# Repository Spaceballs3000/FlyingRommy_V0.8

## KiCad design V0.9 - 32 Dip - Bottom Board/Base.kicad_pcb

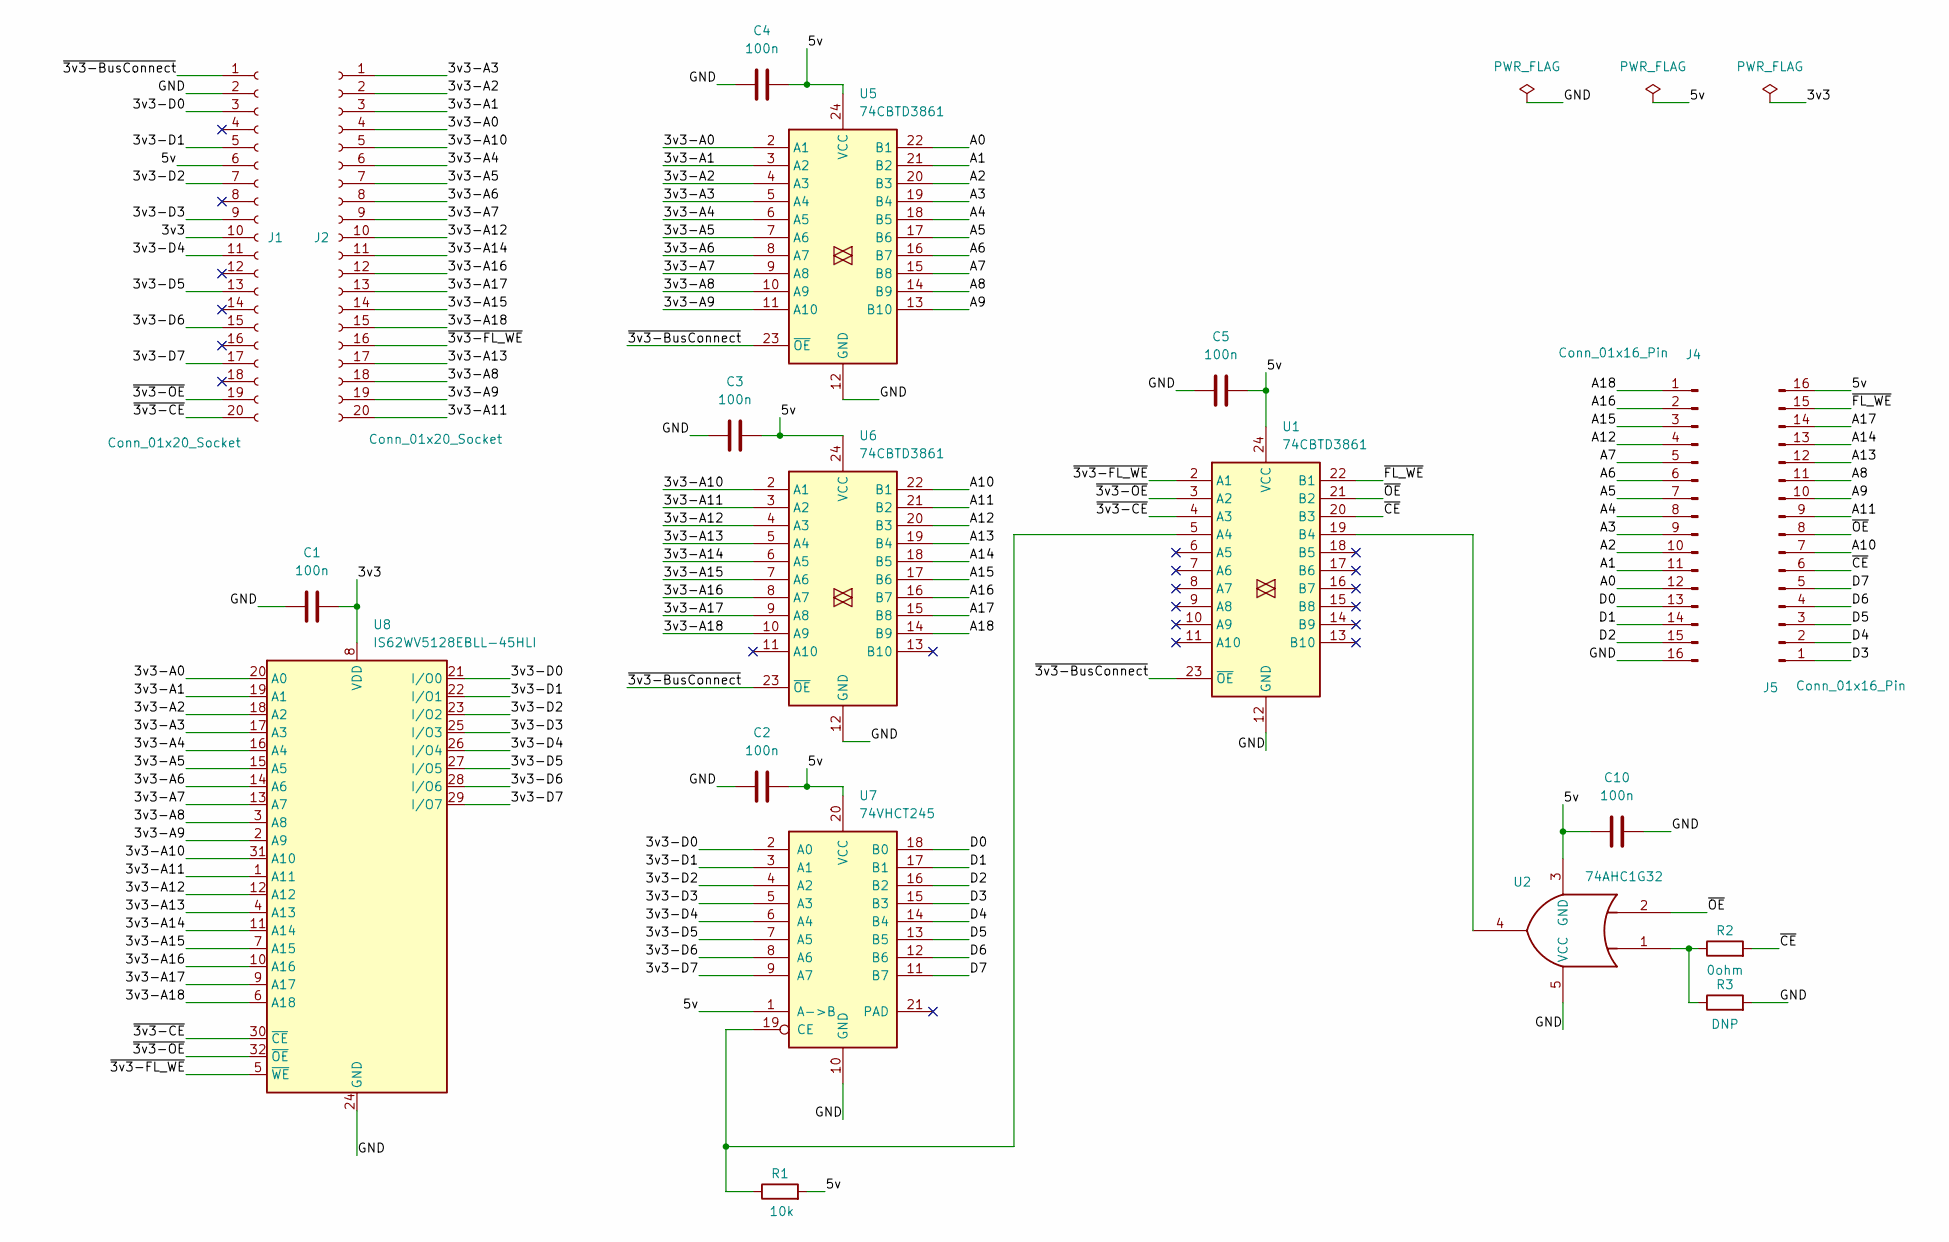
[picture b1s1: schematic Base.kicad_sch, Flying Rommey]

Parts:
C1, C2, C3, C4, C5, C10: 100n; C_0603_1608Metric
J1, J2: Conn_01x20_Socket; PinSocket_2x10_P1.00mm_Vertical_SMD
J4, J5: Conn_01x16_Pin; PinHeader_1x16_P2.54mm_Vertical
R1: 10k; R_0402_1005Metric
R2: 0ohm; R_0402_1005Metric
R3: DNP; R_0402_1005Metric
U1, U5, U6: 74CBTD3861; SSOP-24_3.9x8.7mm_P0.635mm
U2: 74AHC1G32; SOT-353_SC-70-5
U7: 74VHCT245; DHVQFN-20-1EP_2.5x4.5mm_P0.5mm_EP1x3mm
U8: IS62WV5128EBLL-45HLI; TSOP-I-32_11.8x8mm_P0.5mm

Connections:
/3v3: C1.1, J1.10, U8.8 (VDD)
/3v3-A0: J2.4, U5.2 (A1), U8.20 (A0)
/3v3-A1: J2.3, U5.3 (A2), U8.19 (A1)
/3v3-A2: J2.2, U5.4 (A3), U8.18 (A2)
/3v3-A3: J2.1, U5.5 (A4), U8.17 (A3)
/3v3-A4: J2.6, U5.6 (A5), U8.16 (A4)
/3v3-A5: J2.7, U5.7 (A6), U8.15 (A5)
/3v3-A6: J2.8, U5.8 (A7), U8.14 (A6)
/3v3-A7: J2.9, U5.9 (A8), U8.13 (A7)
/3v3-A8: J2.18, U5.10 (A9), U8.3 (A8)
/3v3-A9: J2.19, U5.11 (A10), U8.2 (A9)
/3v3-A10: J2.5, U6.2 (A1), U8.31 (A10)
/3v3-A11: J2.20, U6.3 (A2), U8.1 (A11)
/3v3-A12: J2.10, U6.4 (A3), U8.12 (A12)
/3v3-A13: J2.17, U6.5 (A4), U8.4 (A13)
/3v3-A14: J2.11, U6.6 (A5), U8.11 (A14)
/3v3-A15: J2.14, U6.7 (A6), U8.7 (A15)
/3v3-A16: J2.12, U6.8 (A7), U8.10 (A16)
/3v3-A17: J2.13, U6.9 (A8), U8.9 (A17)
/3v3-A18: J2.15, U6.10 (A9), U8.6 (A18)
/3v3-D0: J1.3, U7.2 (A0), U8.21 (I/O0)
/3v3-D1: J1.5, U7.3 (A1), U8.22 (I/O1)
/3v3-D2: J1.7, U7.4 (A2), U8.23 (I/O2)
/3v3-D3: J1.9, U7.5 (A3), U8.25 (I/O3)
/3v3-D4: J1.11, U7.6 (A4), U8.26 (I/O4)
/3v3-D5: J1.13, U7.7 (A5), U8.27 (I/O5)
/3v3-D6: J1.15, U7.8 (A6), U8.28 (I/O6)
/3v3-D7: J1.17, U7.9 (A7), U8.29 (I/O7)
/5v: C2.1, C3.1, C4.1, C5.1, C10.2, J1.6, J5.16, R1.2, U1.24 (VCC), U2.3 (GND), U5.24 (VCC), U6.24 (VCC), U7.1 (A->B), U7.20 (VCC)
/A0: J4.12, U5.22 (B1)
/A1: J4.11, U5.21 (B2)
/A2: J4.10, U5.20 (B3)
/A3: J4.9, U5.19 (B4)
/A4: J4.8, U5.18 (B5)
/A5: J4.7, U5.17 (B6)
/A6: J4.6, U5.16 (B7)
/A7: J4.5, U5.15 (B8)
/A8: J5.11, U5.14 (B9)
/A9: J5.10, U5.13 (B10)
/A10: J5.7, U6.22 (B1)
/A11: J5.9, U6.21 (B2)
/A12: J4.4, U6.20 (B3)
/A13: J5.12, U6.19 (B4)
/A14: J5.13, U6.18 (B5)
/A15: J4.3, U6.17 (B6)
/A16: J4.2, U6.16 (B7)
/A17: J5.14, U6.15 (B8)
/A18: J4.1, U6.14 (B9)
/D0: J4.13, U7.18 (B0)
/D1: J4.14, U7.17 (B1)
/D2: J4.15, U7.16 (B2)
/D3: J5.1, U7.15 (B3)
/D4: J5.2, U7.14 (B4)
/D5: J5.3, U7.13 (B5)
/D6: J5.4, U7.12 (B6)
/D7: J5.5, U7.11 (B7)
/GND: C1.2, C2.2, C3.2, C4.2, C5.2, C10.1, J1.2, J4.16, R3.2, U1.12 (GND), U2.5 (VCC), U5.12 (GND), U6.12 (GND), U7.10 (GND), U8.24 (GND)
/~3v3-BusConnect: J1.1, U1.23 (~OE), U5.23 (~OE), U6.23 (~OE)
/~3v3-CE: J1.20, U1.4 (A3), U8.30 (~CE)
/~3v3-FL_WE: J2.16, U1.2 (A1), U8.5 (~WE)
/~3v3-OE: J1.19, U1.3 (A2), U8.32 (~OE)
/~CE: J5.6, R2.2, U1.20 (B3)
/~FL_WE: J5.15, U1.22 (B1)
/~OE: J5.8, U1.21 (B2), U2.2
unnamed: R2.1, R3.1, U2.1
unnamed: R1.1, U1.5 (A4), U7.19 (CE)
unnamed: U1.19 (B4), U2.4

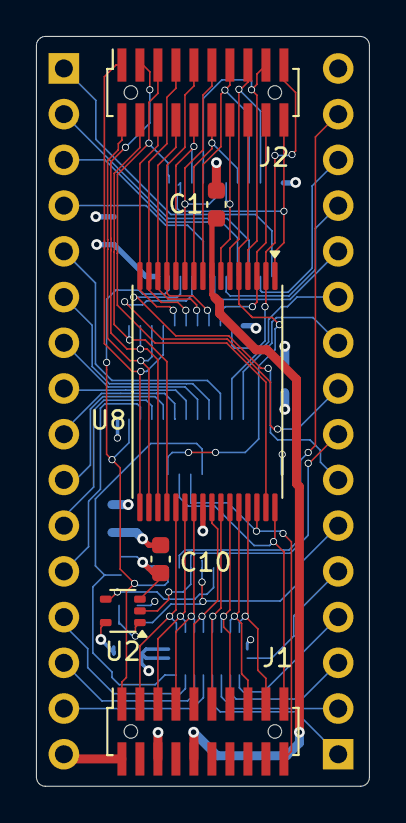
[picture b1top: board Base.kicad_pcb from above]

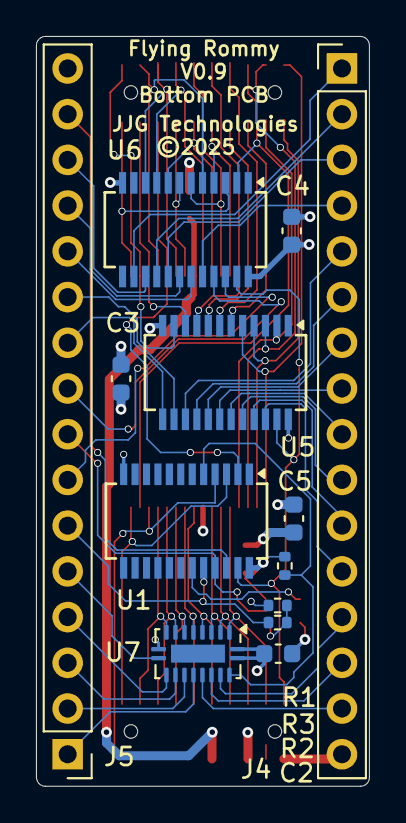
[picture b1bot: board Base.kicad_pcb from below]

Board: 4 copper layers, 18.5 x 41.7 mm, 19 parts (13 on the bottom side), 67 nets.

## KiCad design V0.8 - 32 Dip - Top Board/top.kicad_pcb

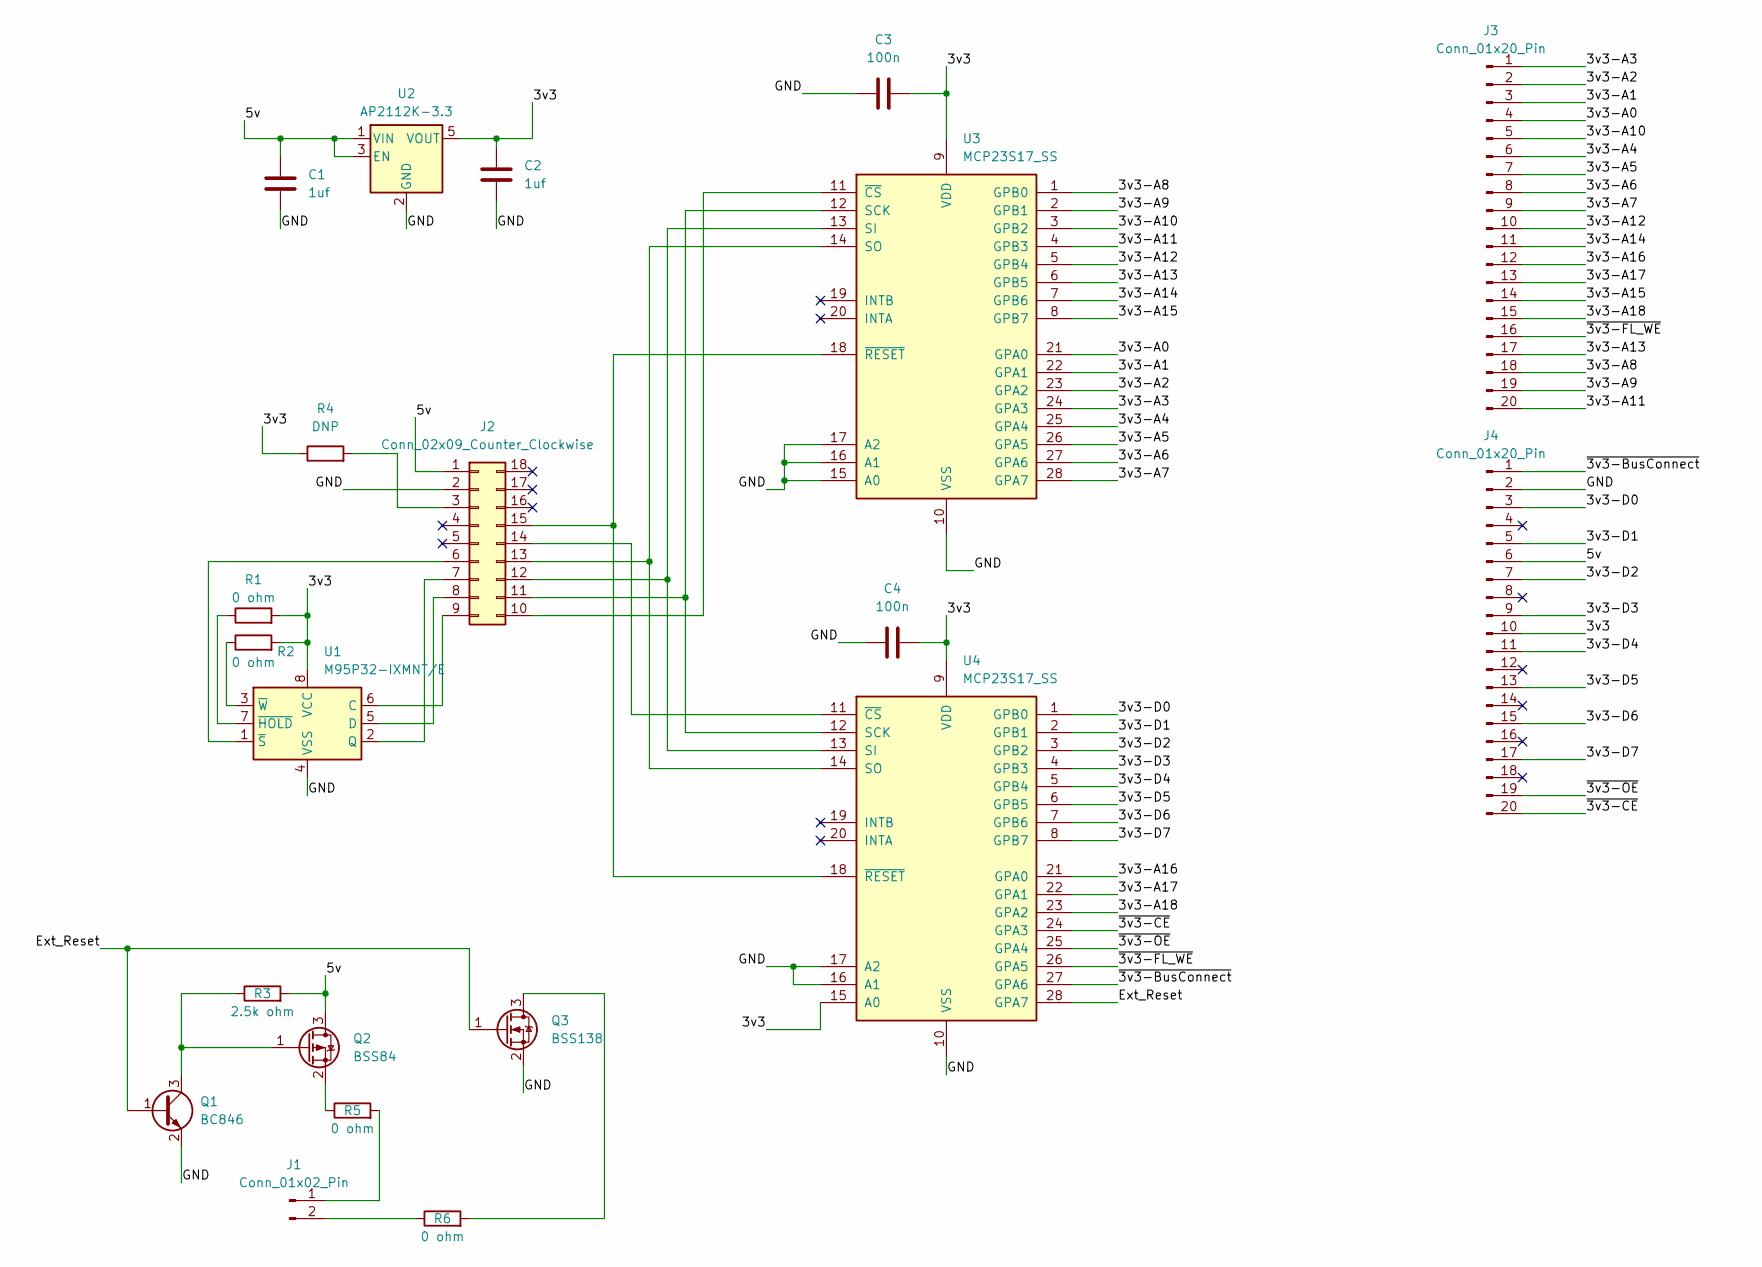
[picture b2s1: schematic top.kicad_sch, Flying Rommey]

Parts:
C1, C2: 1uf; C_0402_1005Metric
C3, C4: 100n; C_0603_1608Metric
J1: Conn_01x02_Pin; PinHeader_1x02_P2.54mm_Horizontal
J2: Conn_02x09_Counter_Clockwise; ESP32
J3, J4: Conn_01x20_Pin; PinHeader_2x10_P1.00mm_Vertical_SMD
Q1: BC846; SOT-23
Q2: BSS84; SOT-23
Q3: BSS138; SOT-23
R1, R2, R5, R6: 0 ohm; R_0402_1005Metric
R3: 2.5k ohm; R_0402_1005Metric
R4: DNP; R_0402_1005Metric
U1: M95P32-IXMNT/E; SOIC-8_3.9x4.9mm_P1.27mm
U2: AP2112K-3.3; SOT-23-5
U3, U4: MCP23S17_SS; SSOP-28_5.3x10.2mm_P0.65mm

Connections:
/3v3: C2.1, C3.1, C4.1, J4.10, R1.2, R2.2, R4.1, U1.8 (VCC), U2.5 (VOUT), U3.9 (VDD), U4.9 (VDD), U4.15 (A0)
/3v3-A0: J3.4, U3.21 (GPA0)
/3v3-A1: J3.3, U3.22 (GPA1)
/3v3-A2: J3.2, U3.23 (GPA2)
/3v3-A3: J3.1, U3.24 (GPA3)
/3v3-A4: J3.6, U3.25 (GPA4)
/3v3-A5: J3.7, U3.26 (GPA5)
/3v3-A6: J3.8, U3.27 (GPA6)
/3v3-A7: J3.9, U3.28 (GPA7)
/3v3-A8: J3.18, U3.1 (GPB0)
/3v3-A9: J3.19, U3.2 (GPB1)
/3v3-A10: J3.5, U3.3 (GPB2)
/3v3-A11: J3.20, U3.4 (GPB3)
/3v3-A12: J3.10, U3.5 (GPB4)
/3v3-A13: J3.17, U3.6 (GPB5)
/3v3-A14: J3.11, U3.7 (GPB6)
/3v3-A15: J3.14, U3.8 (GPB7)
/3v3-A16: J3.12, U4.21 (GPA0)
/3v3-A17: J3.13, U4.22 (GPA1)
/3v3-A18: J3.15, U4.23 (GPA2)
/3v3-D0: J4.3, U4.1 (GPB0)
/3v3-D1: J4.5, U4.2 (GPB1)
/3v3-D2: J4.7, U4.3 (GPB2)
/3v3-D3: J4.9, U4.4 (GPB3)
/3v3-D4: J4.11, U4.5 (GPB4)
/3v3-D5: J4.13, U4.6 (GPB5)
/3v3-D6: J4.15, U4.7 (GPB6)
/3v3-D7: J4.17, U4.8 (GPB7)
/5v: C1.1, J2.1, J4.6, Q2.3 (D), R3.2, U2.1 (VIN), U2.3 (EN)
/Ext_Reset: Q1.1 (B), Q3.1 (G), U4.28 (GPA7)
/GND: C1.2, C2.2, C3.2, C4.2, J2.2, J4.2, Q1.2 (E), Q3.2 (S), U1.4 (VSS), U2.2 (GND), U3.10 (VSS), U3.15 (A0), U3.16 (A1), U3.17 (A2), U4.10 (VSS), U4.16 (A1), U4.17 (A2)
/~3v3-BusConnect: J4.1, U4.27 (GPA6)
/~3v3-CE: J4.20, U4.24 (GPA3)
/~3v3-FL_WE: J3.16, U4.26 (GPA5)
/~3v3-OE: J4.19, U4.25 (GPA4)
unnamed: J1.1, R5.2
unnamed: J1.2, R6.1
unnamed: J2.3, R4.2
unnamed: J2.6, U1.1 (~S)
unnamed: J2.7, U1.2 (Q)
unnamed: J2.8, U1.5 (D)
unnamed: J2.9, U1.6 (C)
unnamed: J2.10, U3.11 (~CS)
unnamed: J2.11, U3.12 (SCK), U4.12 (SCK)
unnamed: J2.12, U3.13 (SI), U4.13 (SI)
unnamed: J2.13, U3.14 (SO), U4.14 (SO)
unnamed: J2.14, U4.11 (~CS)
unnamed: J2.15, U3.18 (~RESET), U4.18 (~RESET)
unnamed: Q1.3 (C), Q2.1 (G), R3.1
unnamed: Q2.2 (S), R5.1
unnamed: Q3.3 (D), R6.2
unnamed: R1.1, U1.7 (~HOLD)
unnamed: R2.1, U1.3 (~W)

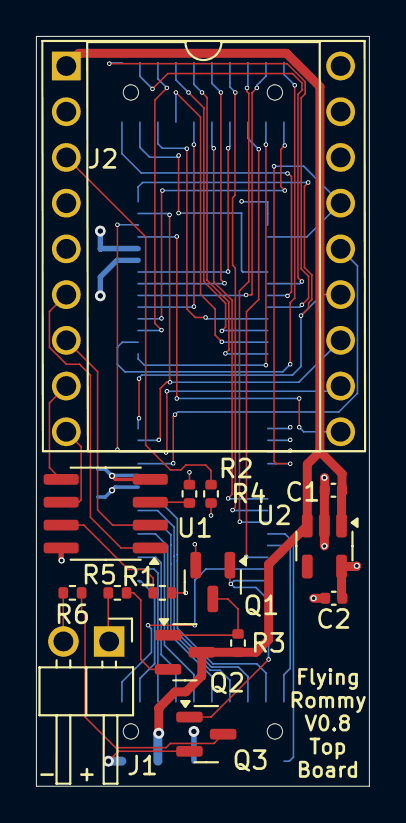
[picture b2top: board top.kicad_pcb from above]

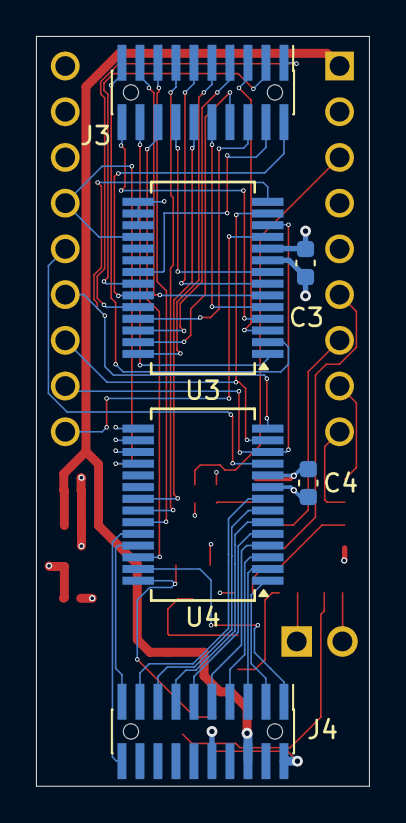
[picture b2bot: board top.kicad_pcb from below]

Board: 4 copper layers, 18.5 x 41.7 mm, 21 parts (6 on the bottom side), 53 nets.

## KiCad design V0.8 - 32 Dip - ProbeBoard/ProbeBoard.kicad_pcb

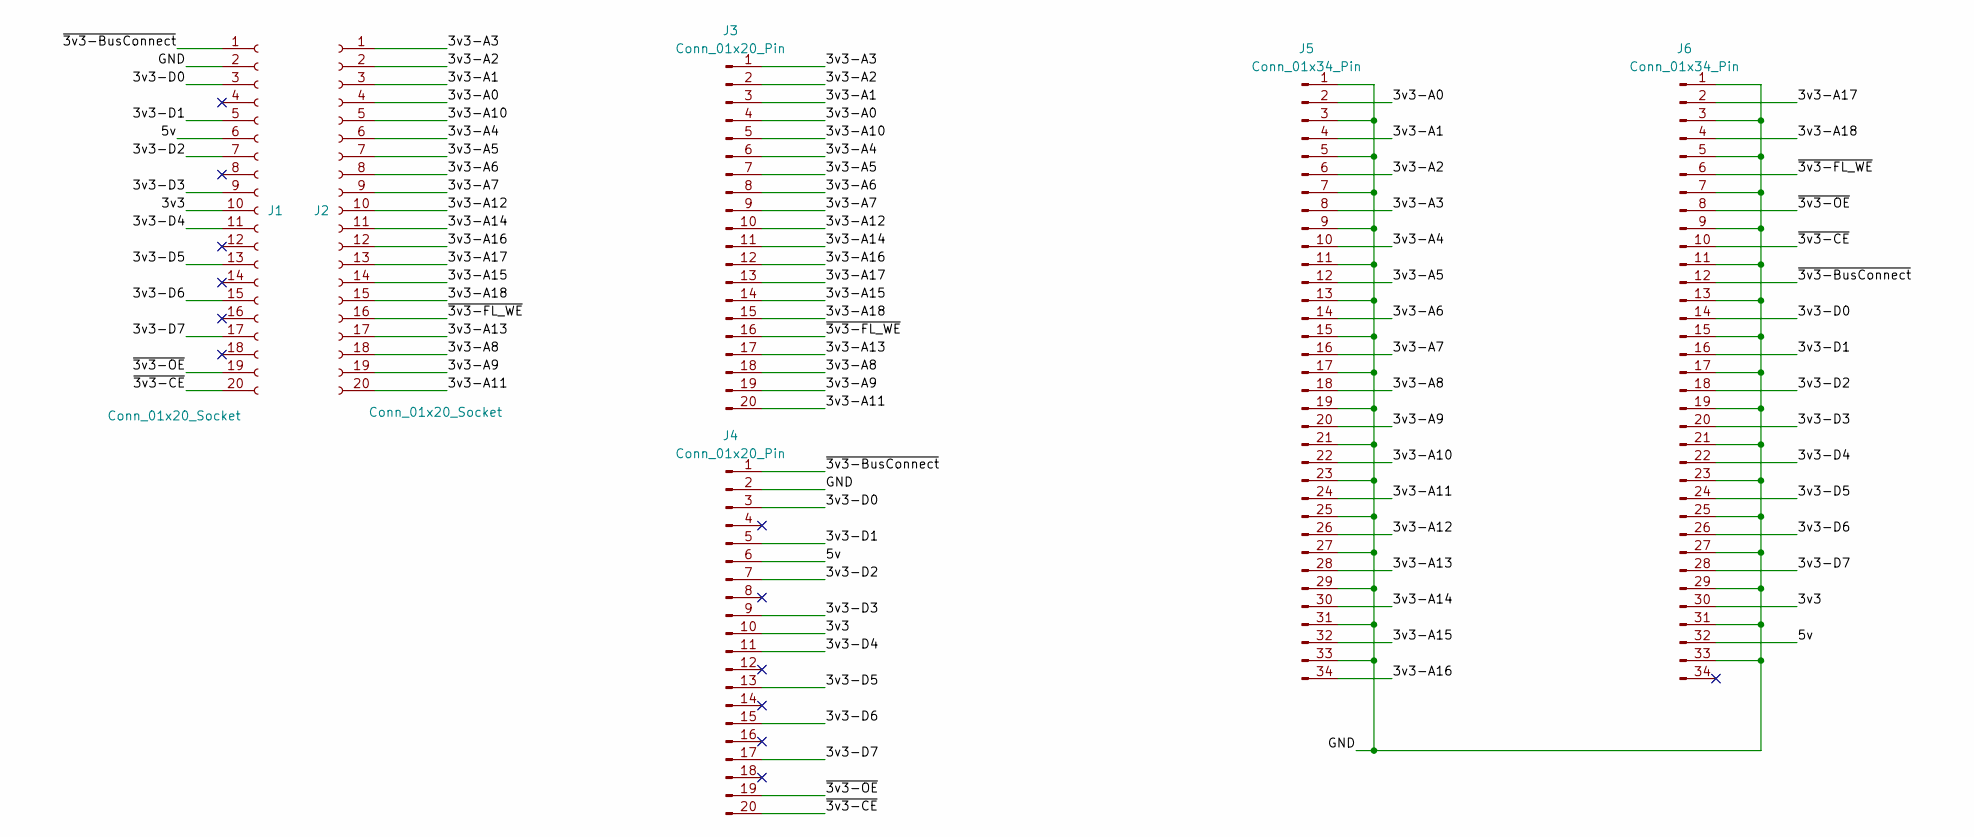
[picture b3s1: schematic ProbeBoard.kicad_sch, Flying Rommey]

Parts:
J1, J2: Conn_01x20_Socket; PinSocket_2x10_P1.00mm_Vertical_SMD
J3, J4: Conn_01x20_Pin; PinHeader_2x10_P1.00mm_Vertical_SMD
J5, J6: Conn_01x34_Pin; PinSocket_2x17_P2.54mm_Vertical

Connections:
/3v3: J1.10, J4.10, J6.30
/3v3-A0: J2.4, J3.4, J5.2
/3v3-A1: J2.3, J3.3, J5.4
/3v3-A2: J2.2, J3.2, J5.6
/3v3-A3: J2.1, J3.1, J5.8
/3v3-A4: J2.6, J3.6, J5.10
/3v3-A5: J2.7, J3.7, J5.12
/3v3-A6: J2.8, J3.8, J5.14
/3v3-A7: J2.9, J3.9, J5.16
/3v3-A8: J2.18, J3.18, J5.18
/3v3-A9: J2.19, J3.19, J5.20
/3v3-A10: J2.5, J3.5, J5.22
/3v3-A11: J2.20, J3.20, J5.24
/3v3-A12: J2.10, J3.10, J5.26
/3v3-A13: J2.17, J3.17, J5.28
/3v3-A14: J2.11, J3.11, J5.30
/3v3-A15: J2.14, J3.14, J5.32
/3v3-A16: J2.12, J3.12, J5.34
/3v3-A17: J2.13, J3.13, J6.2
/3v3-A18: J2.15, J3.15, J6.4
/3v3-D0: J1.3, J4.3, J6.14
/3v3-D1: J1.5, J4.5, J6.16
/3v3-D2: J1.7, J4.7, J6.18
/3v3-D3: J1.9, J4.9, J6.20
/3v3-D4: J1.11, J4.11, J6.22
/3v3-D5: J1.13, J4.13, J6.24
/3v3-D6: J1.15, J4.15, J6.26
/3v3-D7: J1.17, J4.17, J6.28
/5v: J1.6, J4.6, J6.32
/GND: J1.2, J4.2, J5.1, J5.3, J5.5, J5.7, J5.9, J5.11, J5.13, J5.15, J5.17, J5.19, J5.21, J5.23, J5.25, J5.27, J5.29, J5.31, J5.33, J6.1, J6.3, J6.5, J6.7, J6.9, J6.11, J6.13, J6.15, J6.17, J6.19, J6.21, J6.23, J6.25, J6.27, J6.29, J6.31, J6.33
/~3v3-BusConnect: J1.1, J4.1, J6.12
/~3v3-CE: J1.20, J4.20, J6.10
/~3v3-FL_WE: J2.16, J3.16, J6.6
/~3v3-OE: J1.19, J4.19, J6.8

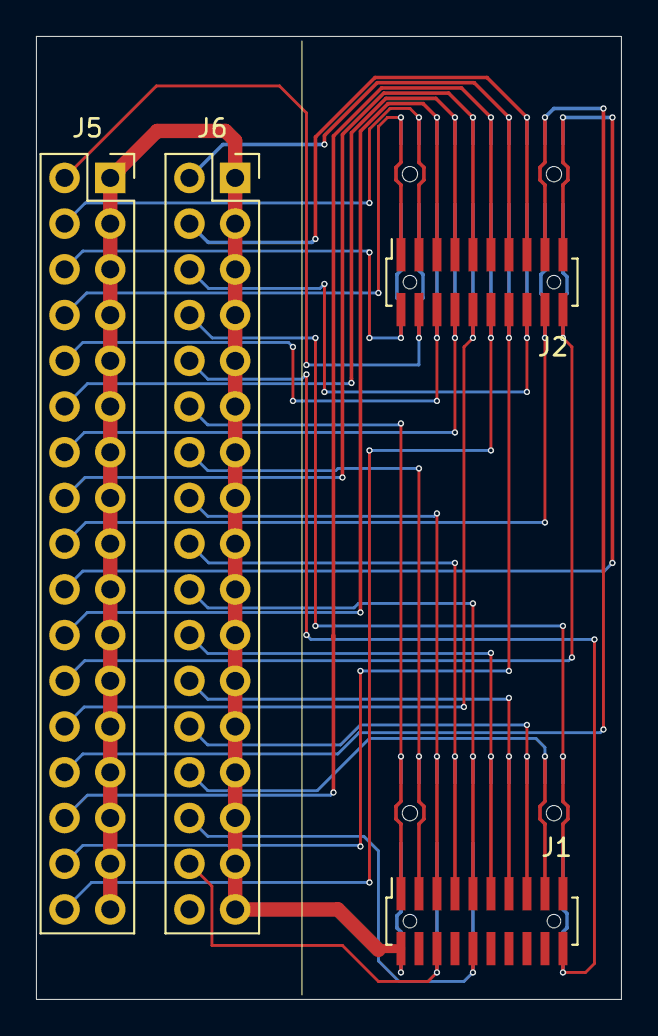
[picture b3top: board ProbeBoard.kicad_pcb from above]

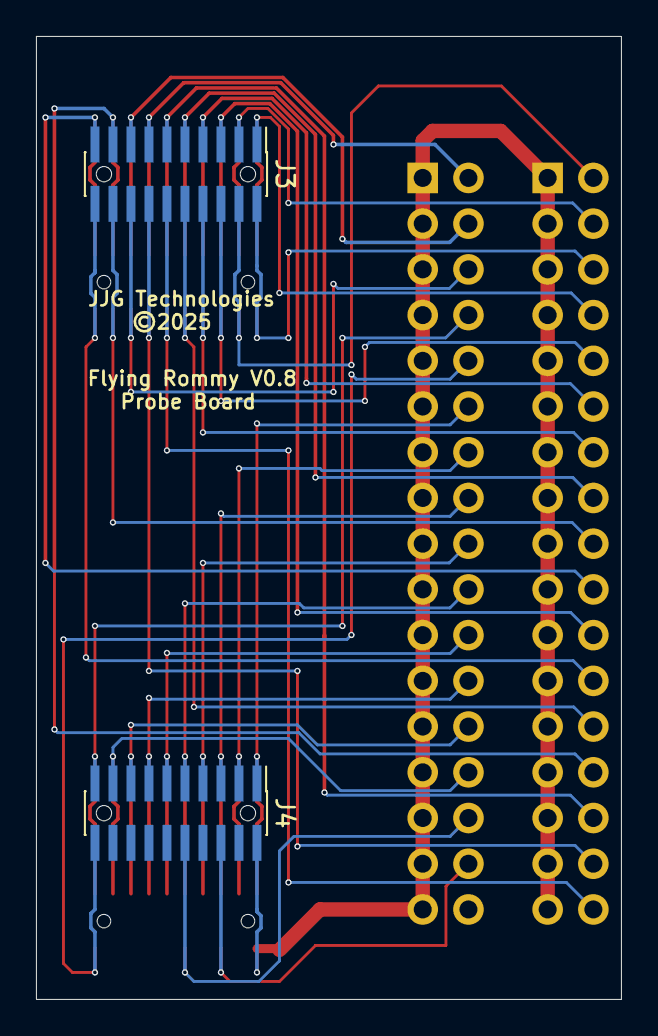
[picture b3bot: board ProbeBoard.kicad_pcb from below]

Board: 2 copper layers, 32.5 x 53.5 mm, 6 parts (2 on the bottom side), 34 nets.

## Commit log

2025-02-13 Updated Bottom PCB
2025-02-14 added mounting holes to 0.1 headers
2025-02-15 Logic OR fix
2025-02-15 Removed Buffer updated Or logic.
2025-02-17 Add Probe PCB, Latest Top/Bottom PCBs
2025-02-19 Made V0.9 Larger VIAs for cheaper boards.

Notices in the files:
V0.8 - 32 Dip - ProbeBoard/ProbeBoard.kicad_pcb:
©2025
